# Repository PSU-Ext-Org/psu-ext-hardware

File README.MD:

<h1 align="center">PSU-EXT Hardware</h1>

<p align="center">
  An open-hardware inline extension that adds measurement, protection, and
  programmable control to an existing bench power supply.
</p>

<p align="center">

</p>

> **EVT prototype:** PSU-EXT is an engineering-validation design, not a
> finished or certified consumer product. It extends a bench PSU; it is not a
> standalone power supply. Use it only within the stated ratings and with
> appropriate laboratory safety practices.

## What it does

PSU-EXT sits between a bench power supply and a load or device under test. It
measures output voltage and current, controls the output path with a relay, and
makes the setup easier to monitor and automate.

- Live voltage, current, and power telemetry
- Relay-controlled output enable/disable
- Galvanically isolated control and measurement domains
- SCPI control over USB CDC and TCP through the companion firmware and software
- External trigger inputs, timer support, and configurable OVP/OCP behaviour

## Hardware at a glance

> **Warning:** PSU-EXT does not provide reverse-polarity protection. Verify
> supply and load polarity before connecting the device.

| Item | Details |
| --- | --- |
| Operating range | 0–25 V, 0–2.5 A |
| Board size | 100 × 50 mm (3.94 × 1.97 in) |
| Control connection | USB-C for power and data |
| Controller | Espressif ESP32-S3 |
| Measurement | ADS1115 ADC and INA240 current-sense front end |
| Isolation | Isolated I²C and isolated DC-DC power for the measurement domain |

## Repository contents

- [`electronics/`](electronics/) — KiCad schematics, PCB, libraries, and the
  [schematic PDF export](electronics/exports/schematic.pdf)
- [`mechanical/`](mechanical/) — FreeCAD enclosure design and label artwork
- [`manufacturing/`](manufacturing/) — Gerbers, BOM, and pick-and-place (CPL)
  files for fabrication and assembly
- [`THIRD-PARTY-NOTICES.md`](THIRD-PARTY-NOTICES.md) — attribution and licence
  information for bundled library assets

The design was created with [**FreeCAD 1.1.1**](https://www.freecad.org/) and
[**KiCad 10.0.1**](https://www.kicad.org/).

## Related PSU-EXT projects

- [PSU-EXT Root](https://github.com/PSU-Ext-Org/psu-ext)
- [Firmware](https://github.com/PSU-Ext-Org/psu-ext-firmware)
- [Control software](https://github.com/PSU-Ext-Org/psu-ext-software)

## Licence

Original PSU-EXT hardware design sources are licensed under the
[CERN Open Hardware Licence Version 2 - Strongly Reciprocal](LICENCE)
(CERN-OHL-S v2). The source location is
<https://github.com/PSU-Ext-Org/psu-ext>.

Some library assets are separately licensed. See [NOTICE](NOTICE),
[THIRD-PARTY-NOTICES.md](THIRD-PARTY-NOTICES.md), and
[LICENSES/dep5](LICENSES/dep5) before copying or modifying them.

Changes to the design are recorded in [CHANGES.txt](CHANGES.txt).

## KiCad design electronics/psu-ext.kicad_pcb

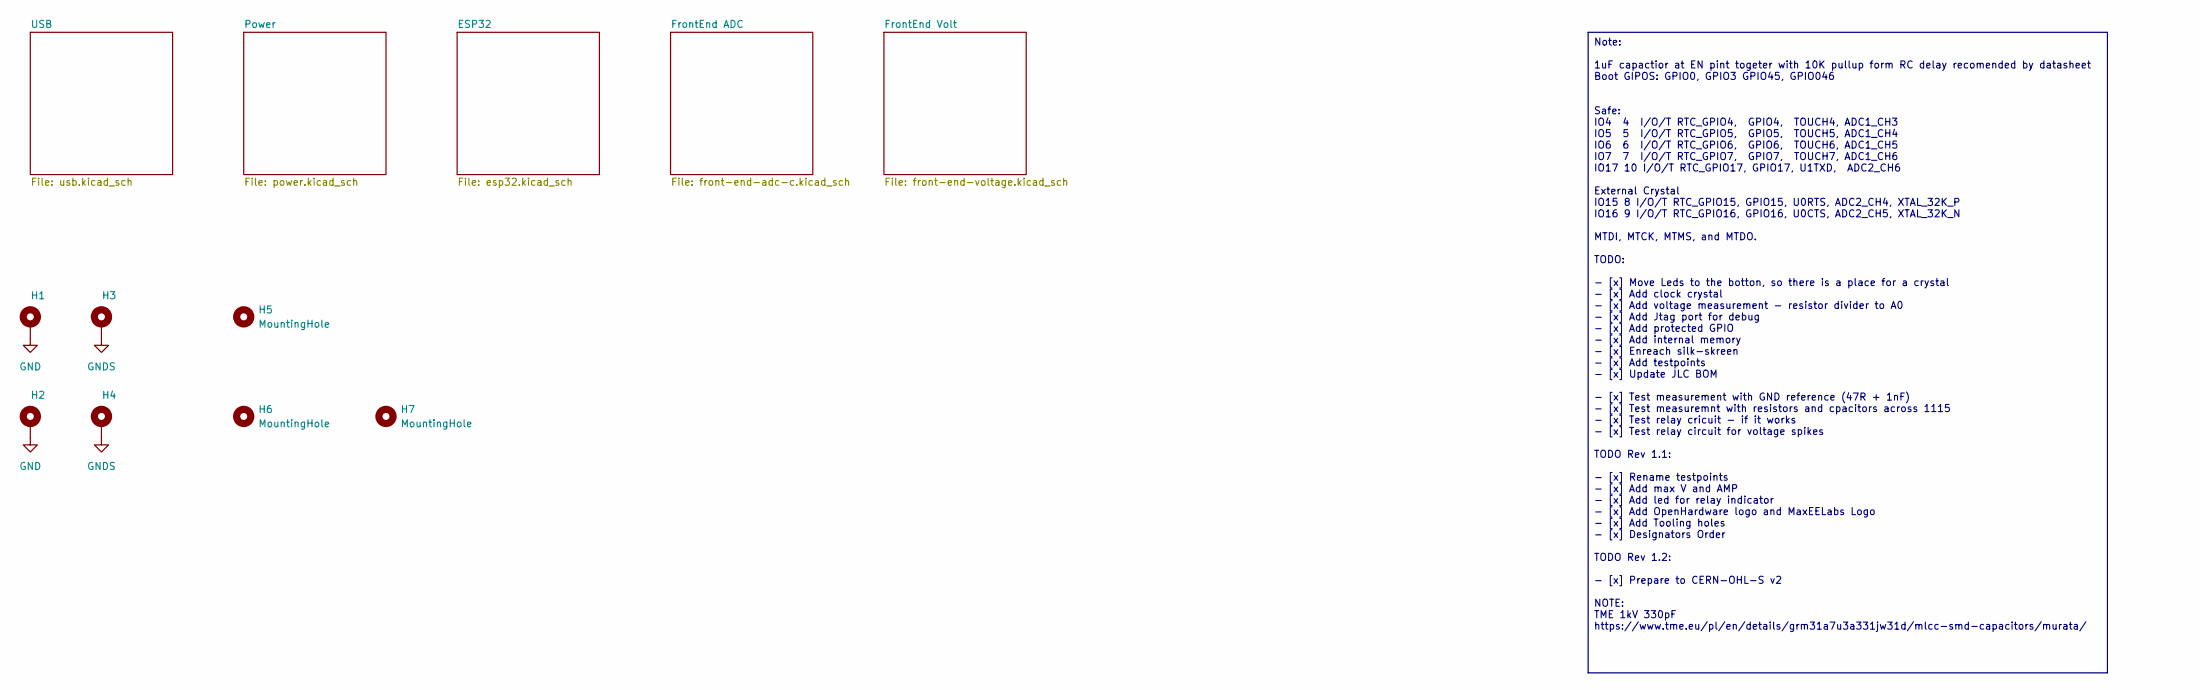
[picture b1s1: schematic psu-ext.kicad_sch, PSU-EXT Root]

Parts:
H1, H2, H3, H4: MountingHole_Pad; MountingHole_3.2mm_M3_ISO7380_Pad
H5, H6, H7: MountingHole; ToolingHole_1.152mm

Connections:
GND: H1.1 (1_1), H2.1 (1_1); also elsewhere on the board
GNDS: H3.1 (1_1), H4.1 (1_1); also elsewhere on the board

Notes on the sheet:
Note: 1uF capactior at EN pint togeter with 10K pullup form RC delay recomended by datasheet Boot GIPOS: GPIO0, GPIO3 GPIO45, GPIO046 Safe: IO4 4 I/O/T RTC_GPIO4, GPIO4, TOUCH4, ADC1_CH3 IO5 5 I/O/T RTC_GPIO5, GPIO5, TOUCH5, ADC1_CH4 IO6 6 I/O/T RTC_GPIO6, GPIO6, TOUCH6, ADC1_CH5 IO7 7 I/O/T RTC_GP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

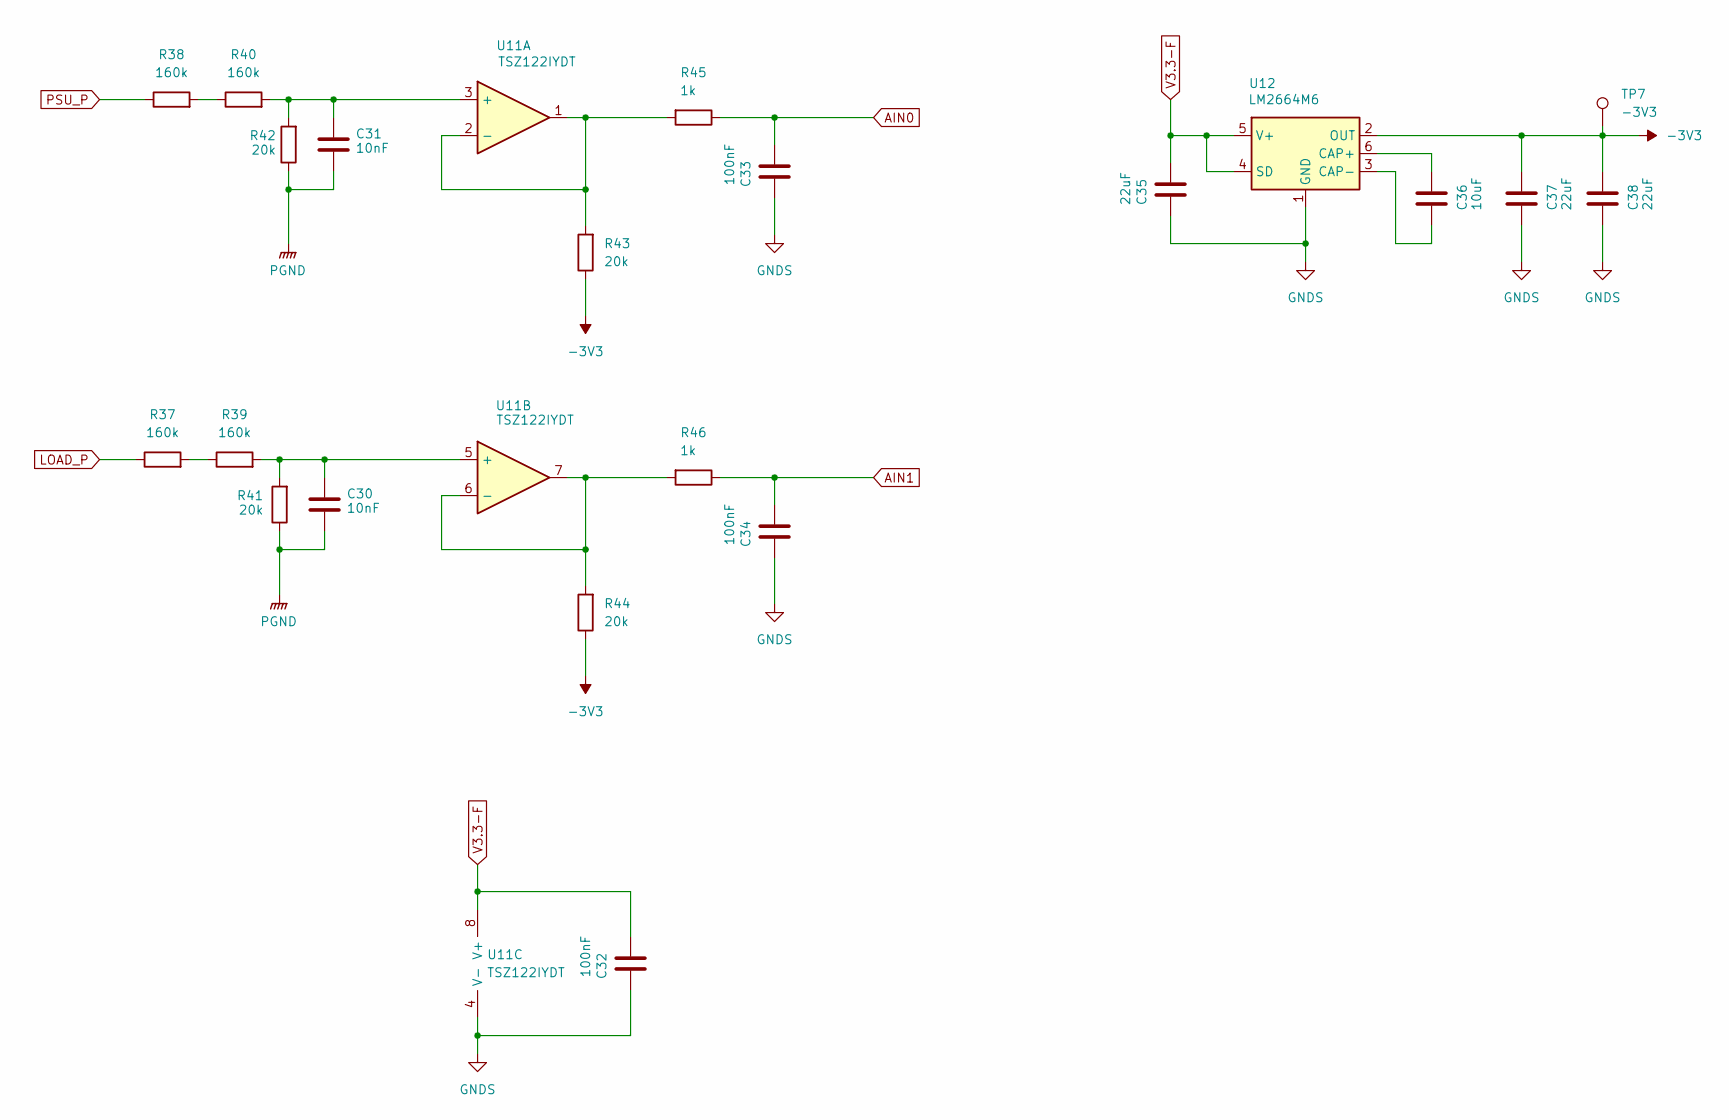
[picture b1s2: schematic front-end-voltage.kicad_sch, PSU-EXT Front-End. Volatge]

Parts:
C30, C31: 10nF; C_0805_2012Metric
C32, C33, C34: 100nF; C_0805_2012Metric
C35, C37, C38: 22uF; C_0805_2012Metric
C36: 10uF; C_0805_2012Metric
R37, R38, R39, R40: 160k; R_0805_2012Metric
R41, R42, R43, R44: 20k; R_0805_2012Metric
R45, R46: 1k; R_0805_2012Metric
TP7: -3V3; TestPoint_Pad_D1.5mm
U11: TSZ122IYDT; SOIC-8_3.9x4.9mm_P1.27mm
U12: LM2664M6; SOT-23-6

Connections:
-3V3: C37.1, C38.1, R43.1, R44.1, TP7.1 (1_1), U12.2 (OUT)
AIN0: C33.1, R45.1; also elsewhere on the board
AIN1: C34.1, R46.1; also elsewhere on the board
GNDS: C32.2, C33.2, C34.2, C35.2, C37.2, C38.2, U11.4 (V-), U12.1 (GND); also elsewhere on the board
LOAD_P: R37.1; also elsewhere on the board
unnamed: R37.2, R39.1
unnamed: R38.2, R40.1
unnamed: C31.1, R40.2, R42.2, U11.3 (+)
unnamed: R43.2, R45.2, U11.1, U11.2 (-)
unnamed: C30.1, R39.2, R41.2, U11.5 (+)
unnamed: R44.2, R46.2, U11.6 (-), U11.7
unnamed: C36.1, U12.6 (CAP+)
unnamed: C36.2, U12.3 (CAP-)
PGND: C30.2, C31.2, R41.1, R42.1; also elsewhere on the board
PSU_P: R38.1; also elsewhere on the board
V3.3-F: C32.1, C35.1, U11.8 (V+), U12.4 (SD), U12.5 (V+); also elsewhere on the board

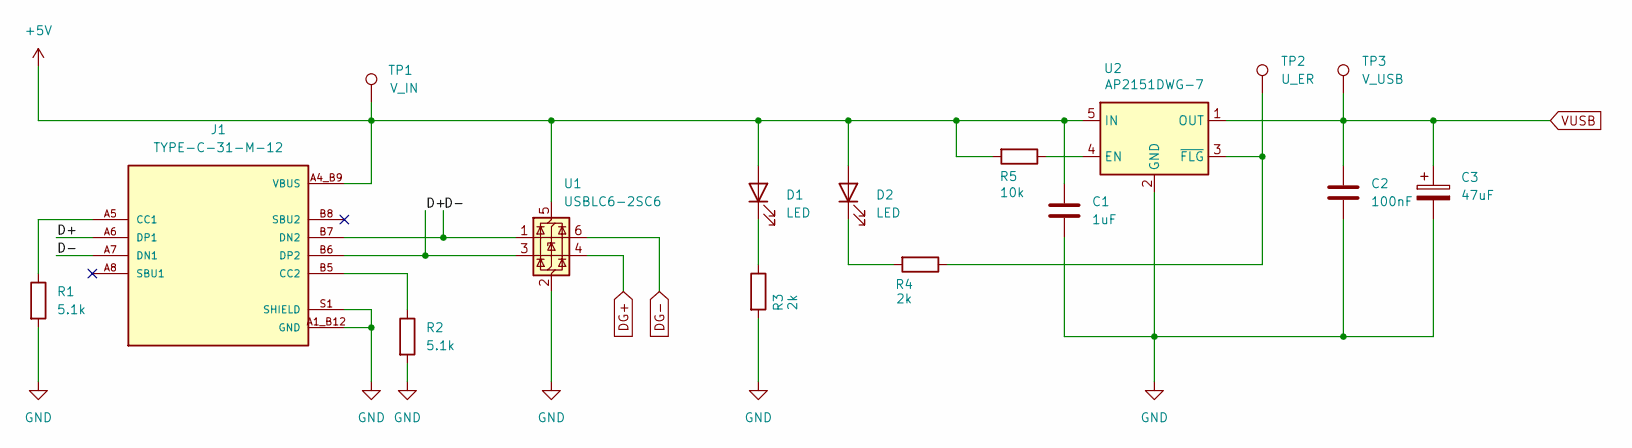
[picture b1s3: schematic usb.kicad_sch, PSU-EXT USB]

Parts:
C1: 1uF; C_0805_2012Metric
C2: 100nF; C_0805_2012Metric
C3: 47uF; CP_Elec_5x5.9
D1, D2: LED; LED_0805_2012Metric
J1: TYPE-C-31-M-12; HRO_TYPE-C-31-M-12; PARTREV 2020.12.08
R1, R2: 5.1k; R_0805_2012Metric
R3, R4: 2k; R_0805_2012Metric
R5: 10k; R_0805_2012Metric
TP1: V_IN; TestPoint_Pad_D1.5mm
TP2: U_ER; TestPoint_Pad_D1.5mm
TP3: V_USB; TestPoint_Pad_D1.5mm
U1: USBLC6-2SC6; SOT-23-6
U2: AP2151DWG-7; SOT-23-5

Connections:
+5V: C1.1, D1.2 (A), D2.2 (A), J1.A4_B9 (VBUS), J1.B4_A9 (VBUS), R5.2, TP1.1 (1_1), U1.5 (VBUS), U2.5 (IN)
/USB/D+: J1.A6 (DP1), J1.B6 (DP2), U1.3 (I/O2)
/USB/D-: J1.A7 (DN1), J1.B7 (DN2), U1.1 (I/O1)
DG+: U1.4 (I/O2); also elsewhere on the board
DG-: U1.6 (I/O1); also elsewhere on the board
GND: C1.2, C2.2, C3.2, J1.A1_B12 (GND), J1.B1_A12 (GND), J1.S1 (SHIELD), J1.S2 (SHIELD), J1.S3 (SHIELD), J1.S4 (SHIELD), R1.2, R2.2, R3.2, U1.2 (GND), U2.2 (GND); also elsewhere on the board
unnamed: D1.1 (K), R3.1
unnamed: D2.1 (K), R4.2
unnamed: J1.A5 (CC1), R1.1
unnamed: J1.B5 (CC2), R2.1
unnamed: R5.1, U2.4 (EN)
unnamed: R4.1, TP2.1 (1_1), U2.3 (~FLG)
VUSB: C2.1, C3.1, TP3.1 (1_1), U2.1 (OUT); also elsewhere on the board

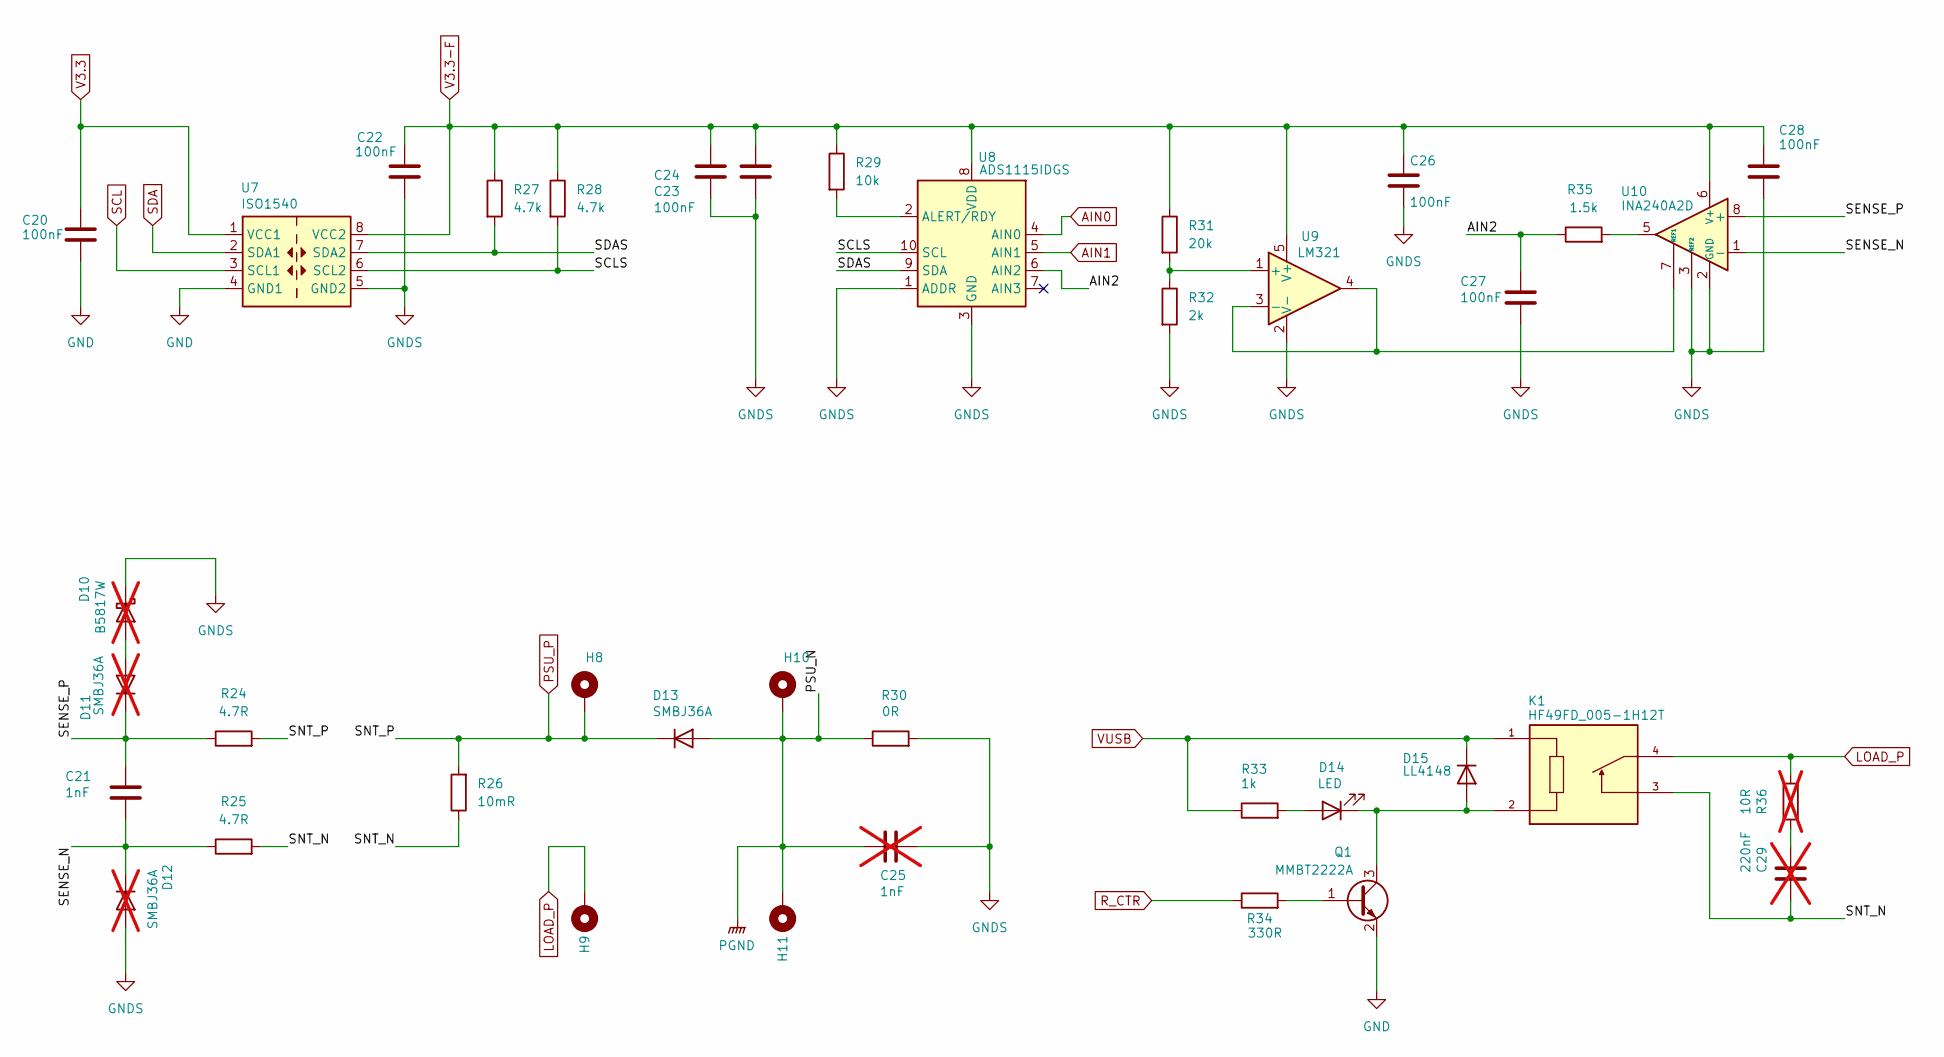
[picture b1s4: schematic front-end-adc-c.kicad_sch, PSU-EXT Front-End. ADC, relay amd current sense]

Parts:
C20, C22, C23, C24, C26, C27, C28: 100nF; C_0805_2012Metric
C21: 1nF; C_0805_2012Metric
C25: 1nF; C_0805_2012Metric; not fitted
C29: 220nF; C_0805_2012Metric; not fitted
D10: B5817W; Nexperia_CFP3_SOD-123W; not fitted
D11, D12: SMBJ36A; D_SMB; not fitted
D13: SMBJ36A; D_SMB
D14: LED; LED_0805_2012Metric
D15: LL4148; D_MiniMELF
H8, H9, H10, H11: MountingHole_Pad; MountingHole_4.3mm_M4_ISO7380_Pad
K1: HF49FD_005-1H12T; RELAY_HF49FD_005-1H12T; PARTREV 1.13
Q1: MMBT2222A; SOT-23
R24, R25: 4.7R; R_0805_2012Metric
R26: 10mR; R_2512_6332Metric_Pad1.40x3.35mm_HandSolder
R27, R28: 4.7k; R_0805_2012Metric
R29: 10k; R_0805_2012Metric
R30: 0R; R_0805_2012Metric
R31: 20k; R_0805_2012Metric
R32: 2k; R_0805_2012Metric
R33: 1k; R_0805_2012Metric
R34: 330R; R_0805_2012Metric
R35: 1.5k; R_0805_2012Metric
R36: 10R; R_0805_2012Metric; not fitted
U7: ISO1540; SOIC-8_3.9x4.9mm_P1.27mm
U8: ADS1115IDGS; TSSOP-10_3x3mm_P0.5mm
U9: LM321; SOT-23-5
U10: INA240A2D; SOIC-8_3.9x4.9mm_P1.27mm

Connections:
/FrontEnd ADC/AIN2: C27.1, R35.1, U8.6 (AIN2)
/FrontEnd ADC/SCLS: R28.2, U7.6 (SCL2), U8.10 (SCL)
/FrontEnd ADC/SDAS: R27.2, U7.7 (SDA2), U8.9 (SDA)
/FrontEnd ADC/SENSE_N: C21.2, D12.1 (K), R25.1, U10.1 (-)
/FrontEnd ADC/SENSE_P: C21.1, D11.1 (K), R24.1, U10.8 (+)
/FrontEnd ADC/SNT_N: C29.2, K1.3, R25.2, R26.1
AIN0: U8.4 (AIN0); also elsewhere on the board
AIN1: U8.5 (AIN1); also elsewhere on the board
GND: C20.2, Q1.2 (E), U7.4 (GND1); also elsewhere on the board
GNDS: C22.2, C23.2, C24.2, C25.2, C26.2, C27.2, C28.2, D10.1 (K), D12.2 (A), R30.2, R32.2, U7.5 (GND2), U8.1 (ADDR), U8.3 (GND), U9.2 (V-), U10.2 (GND), U10.3 (REF2), U10.4 (GND); also elsewhere on the board
LOAD_P: H9.1 (1_1), K1.4, R36.1; also elsewhere on the board
unnamed: C29.1, R36.2
unnamed: D10.2 (A), D11.2 (A)
unnamed: D14.2 (A), R33.2
unnamed: D14.1 (K), D15.2 (A), K1.2, Q1.3 (C)
unnamed: Q1.1 (B), R34.2
unnamed: R35.2, U10.5
unnamed: R29.2, U8.2 (ALERT/RDY)
unnamed: R31.2, R32.1, U9.1 (+)
unnamed: U9.3 (-), U9.4, U10.7 (REF1)
PGND: C25.1, D13.2 (A), H10.1 (1_1), H11.1 (1_1), R30.1; also elsewhere on the board
PSU_P: D13.1 (K), H8.1 (1_1), R24.2, R26.2; also elsewhere on the board
R_CTR: R34.1; also elsewhere on the board
SCL: U7.3 (SCL1); also elsewhere on the board
SDA: U7.2 (SDA1); also elsewhere on the board
V3.3: C20.1, U7.1 (VCC1); also elsewhere on the board
V3.3-F: C22.1, C23.1, C24.1, C26.1, C28.1, R27.1, R28.1, R29.1, R31.1, U7.8 (VCC2), U8.8 (VDD), U9.5 (V+), U10.6 (V+); also elsewhere on the board
VUSB: D15.1 (K), K1.1, R33.1; also elsewhere on the board

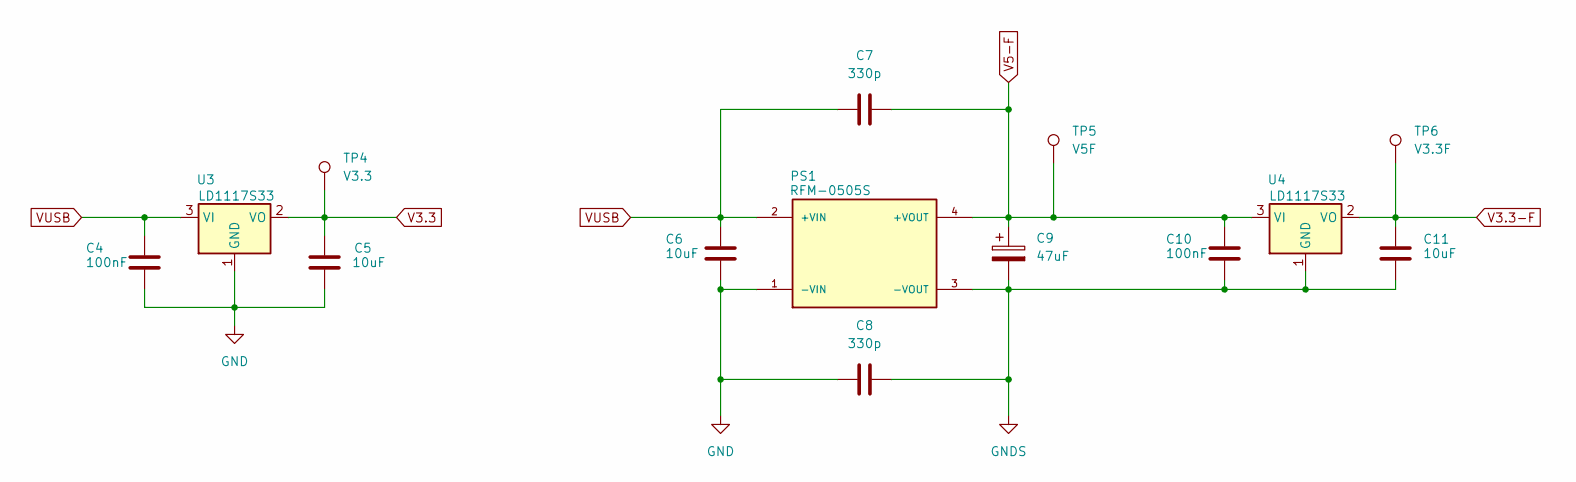
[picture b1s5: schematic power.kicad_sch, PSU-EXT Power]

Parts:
C4, C10: 100nF; C_0805_2012Metric
C5, C11: 10uF; C_1206_3216Metric
C6: 10uF; C_0805_2012Metric
C7, C8: 330p; C_1206_3216Metric_Pad1.33x1.80mm_HandSolder
C9: 47uF; CP_Elec_5x5.9
PS1: RFM-0505S; CONV_RFM-0505S; PARTREV 0
TP4: V3.3; TestPoint_Pad_D1.5mm
TP5: V5F; TestPoint_Pad_D1.5mm
TP6: V3.3F; TestPoint_Pad_D1.5mm
U3, U4: LD1117S33; SOT-223-3_TabPin2

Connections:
GND: C4.2, C5.2, C6.2, C8.1, PS1.1 (-VIN), U3.1 (GND); also elsewhere on the board
GNDS: C8.2, C9.2, C10.2, C11.2, PS1.3 (-VOUT), U4.1 (GND); also elsewhere on the board
V3.3: C5.1, TP4.1 (1_1), U3.2 (VO); also elsewhere on the board
V3.3-F: C11.1, TP6.1 (1_1), U4.2 (VO); also elsewhere on the board
V5-F: C7.2, C9.1, C10.1, PS1.4 (+VOUT), TP5.1 (1_1), U4.3 (VI)
VUSB: C4.1, C6.1, C7.1, PS1.2 (+VIN), U3.3 (VI); also elsewhere on the board

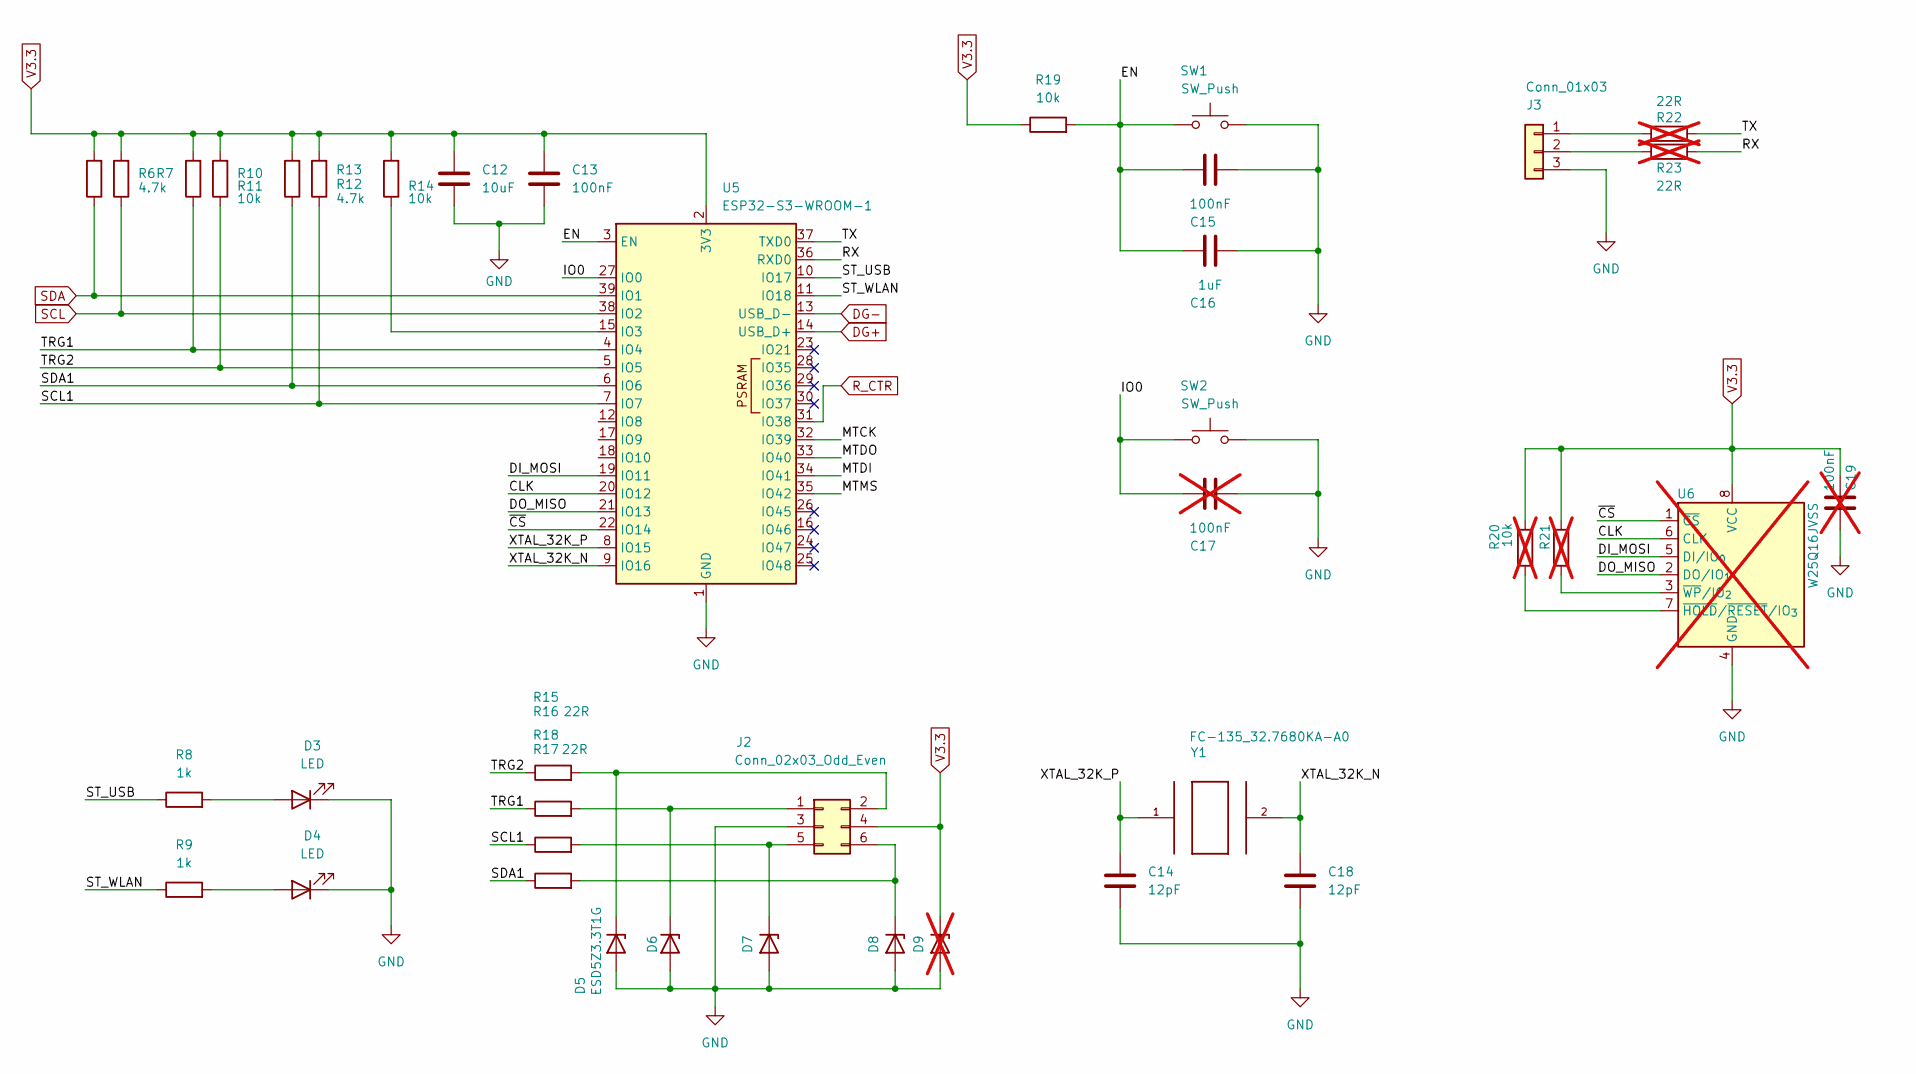
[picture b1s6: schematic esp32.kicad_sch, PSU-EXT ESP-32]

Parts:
C12: 10uF; C_0805_2012Metric
C13, C15: 100nF; C_0805_2012Metric
C14, C18: 12pF; C_0805_2012Metric
C16: 1uF; C_0805_2012Metric
C17, C19: 100nF; C_0805_2012Metric; not fitted
D3, D4: LED; LED_0805_2012Metric
D5, D6, D7, D8: ESD5Z3.3T1G; D_SOD-523
D9: ESD5Z3.3T1G; D_SOD-523; not fitted
J2: Conn_02x03_Odd_Even; PinHeader_2x03_P2.54mm_Vertical
J3: Conn_01x03; PinHeader_1x03_P2.54mm_Vertical
R6, R7, R12, R13: 4.7k; R_0805_2012Metric
R8, R9: 1k; R_0805_2012Metric
R10, R11, R14, R19: 10k; R_0805_2012Metric
R15, R16, R17, R18: 22R; R_0805_2012Metric
R20, R21: 10k; R_0805_2012Metric; not fitted
R22, R23: 22R; R_0805_2012Metric; not fitted
SW1, SW2: SW_Push; SW_SPST_TS-1088-xR025
U5: ESP32-S3-WROOM-1
U6: W25Q16JVSS; SOIC-8_5.3x5.3mm_P1.27mm; not fitted
Y1: FC-135_32.7680KA-A0; XTAL_FC-135_32.7680KA-A0

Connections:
/ESP32/CLK: U5.20 (IO12), U6.6 (CLK)
/ESP32/DI_MOSI: U5.19 (IO11), U6.5 (DI/IO_{0})
/ESP32/DO_MISO: U5.21 (IO13), U6.2 (DO/IO_{1})
/ESP32/EN: C15.1, C16.1, R19.2, SW1.1, U5.3 (EN)
/ESP32/IO0: C17.1, SW2.1, U5.27 (IO0)
/ESP32/MTCK: U5.32 (IO39)
/ESP32/MTDI: U5.34 (IO41)
/ESP32/MTDO: U5.33 (IO40)
/ESP32/MTMS: U5.35 (IO42)
/ESP32/RX: R23.2, U5.36 (RXD0)
/ESP32/SCL1: R13.1, R17.1, U5.7 (IO7)
/ESP32/SDA1: R12.1, R18.1, U5.6 (IO6)
/ESP32/ST_USB: R8.1, U5.10 (IO17)
/ESP32/ST_WLAN: R9.1, U5.11 (IO18)
/ESP32/TRG1: R10.1, R16.1, U5.4 (IO4)
/ESP32/TRG2: R11.1, R15.1, U5.5 (IO5)
/ESP32/TX: R22.2, U5.37 (TXD0)
/ESP32/XTAL_32K_N: C18.1, U5.9 (IO16), Y1.2
/ESP32/XTAL_32K_P: C14.1, U5.8 (IO15), Y1.1
/ESP32/~CS: U5.22 (IO14), U6.1 (~CS)
DG+: U5.14 (USB_D+); also elsewhere on the board
DG-: U5.13 (USB_D-); also elsewhere on the board
GND: C12.2, C13.2, C14.2, C15.2, C16.2, C17.2, C18.2, C19.1, D3.1 (K), D4.1 (K), D5.2 (A), D6.2 (A), D7.2 (A), D8.2 (A), D9.2 (A), J2.3, J3.3, SW1.2, SW2.2, U5.1 (GND), U5.40 (GND), U5.41 (GND), U6.4 (GND); also elsewhere on the board
unnamed: D3.2 (A), R8.2
unnamed: D4.2 (A), R9.2
unnamed: D5.1 (K), J2.2, R15.2
unnamed: D6.1 (K), J2.1, R16.2
unnamed: D7.1 (K), J2.5, R17.2
unnamed: D8.1 (K), J2.6, R18.2
unnamed: J3.1, R22.1
unnamed: J3.2, R23.1
unnamed: R14.1, U5.15 (IO3)
unnamed: R20.2, U6.7 (~HOLD/~RESET/IO_{3})
unnamed: R21.2, U6.3 (~WP/IO_{2})
R_CTR: U5.31 (IO38); also elsewhere on the board
SCL: R7.1, U5.38 (IO2); also elsewhere on the board
SDA: R6.1, U5.39 (IO1); also elsewhere on the board
V3.3: C12.1, C13.1, C19.2, D9.1 (K), J2.4, R6.2, R7.2, R10.2, R11.2, R12.2, R13.2, R14.2, R19.1, R20.1, R21.1, U5.2 (3V3), U6.8 (VCC); also elsewhere on the board

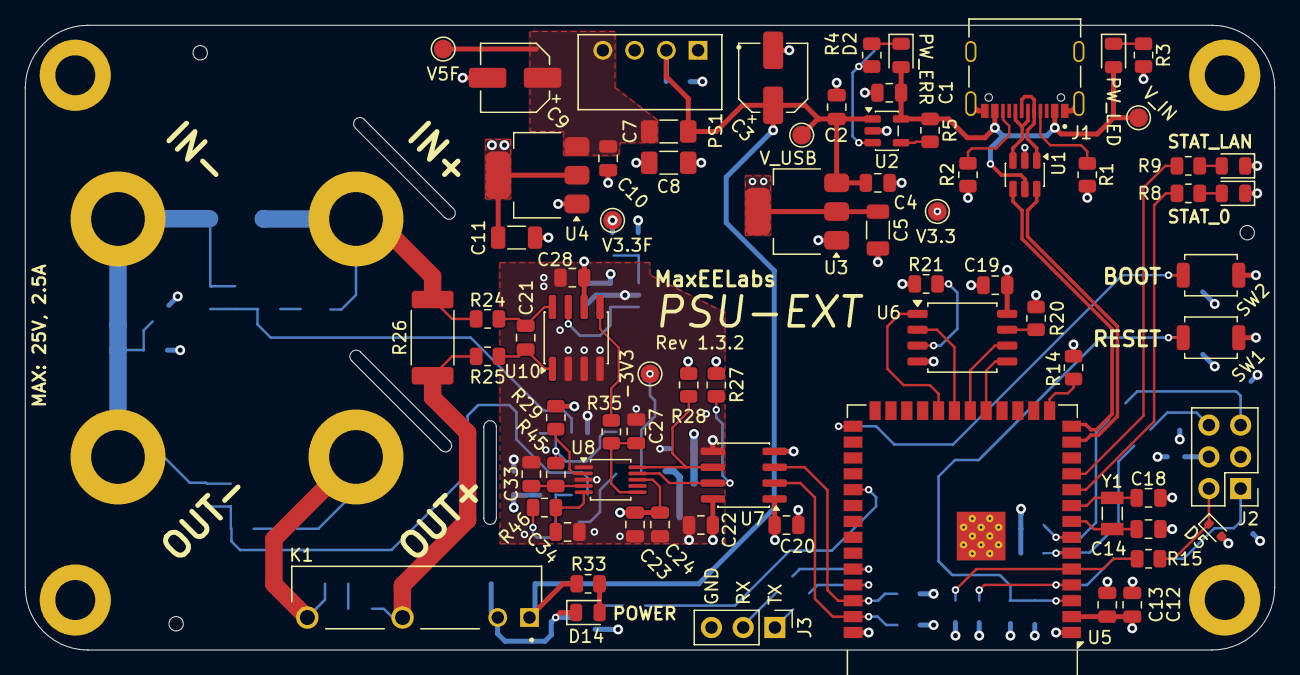
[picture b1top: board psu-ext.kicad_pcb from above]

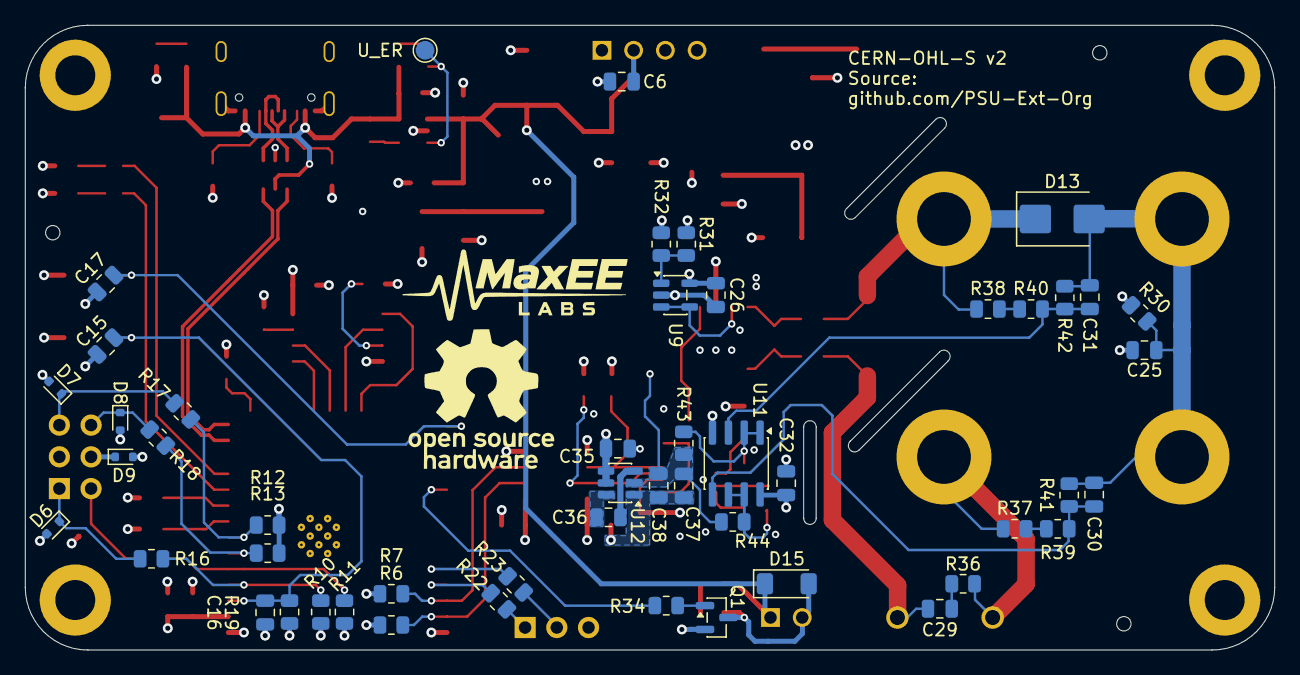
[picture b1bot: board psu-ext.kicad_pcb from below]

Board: 4 copper layers, 100.0 x 50.0 mm, 137 parts (52 on the bottom side), 75 nets.

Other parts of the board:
G1: LOGO; logo_oshw_22x13.2mm
G2: LOGO; logo_20x11.2mm

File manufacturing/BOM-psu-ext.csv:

*Reference,*Manufacturer Part number,*QTY,*Original,Description,Purchase Link
R30,0805W8F0000T5E,1,Y,0Ω ±1% 125mW 0805 Thick Film Resistor,
R35,0805W8F1501T5E,1,Y,1.5kΩ ±1% 125mW 0805 Thick Film Resistor,
"C10,C13,C15,C2,C20,C22,C23,C24,C26,C27,C28,C32,C33,C34,C4",CC0805KRX7R9BB104,15,Y,100nF ±10% 50V Ceramic Capacitor X7R 0805,
"R10,R11,R14,R19,R29,R5",0805W8F1002T5E,6,Y,10kΩ ±1% 125mW 0805 Thick Film Resistor,
R26,25121WF100MT4E,1,Y,10mΩ 1W 200V Thick Film Resistor ±1500ppm/℃ ±1% 2512 Chip Resistor - Surface Mount RoHS,
"C30,C31",CL21B103KBANNNC,2,Y,10nF ±10% 50V Ceramic Capacitor X7R 0805,
"C11,C5",CL31A106KBHNNNE,2,Y,10uF ±10% 50V Ceramic Capacitor X5R 1206,
"C12,C36,C6",CL21A106KAYNNNE,3,Y,10uF ±10% 25V Ceramic Capacitor X5R 0805,
"C14,C18",CC0805JRNPO9BN120,2,Y,12pF ±5% 50V Ceramic Capacitor NP0 0805,
"R37,R38,R39,R40",FRC0805J164 TS,4,Y,160kΩ ±5% 125mW 0805 Thick Film Resistor,
"R33,R45,R46,R8,R9",0805W8F1001T5E,5,Y,1kΩ ±1% 125mW 0805 Thick Film Resistor,
C21,CL21B102KBCNNNC,1,Y,1nF ±10% 50V Ceramic Capacitor X7R 0805,
"C1,C16",CL21B105KBFNNNE,2,Y,1uF ±10% 50V Ceramic Capacitor X7R 0805,
"R31,R41,R42,R43,R44",0805W8F2002T5E,5,Y,20kΩ ±1% 125mW 0805 Thick Film Resistor,
"R15,R16,R17,R18",0805W8F220JT5E,4,Y,22Ω ±1% 125mW 0805 Thick Film Resistor,
"C35,C37,C38",CL21A226MAQNNNE,3,Y,22uF ±20% 25V Ceramic Capacitor X5R 0805,
"R3,R32,R4",0805W8J0202T5E,3,Y,2kΩ ±5% 125mW 0805 Thick Film Resistor,
R34,0805W8F3300T5E,1,Y,330Ω ±1% 125mW 0805 Thick Film Resistor,
"C7,C8",TCC1206COG331J102DT,2,Y,330pF ±5% 1kV Ceramic Capacitor C0G 1206,
"R24,R25",0805W8F470KT5E,2,Y,4.7Ω ±1% 125mW 0805 Thick Film Resistor,
"R12,R13,R27,R28,R6,R7",0805W8F4701T5E,6,Y,4.7kΩ ±1% 125mW 0805 Thick Film Resistor,
"C3,C9",189RV0006,2,Y,47uF ±20% 35V Aluminum Electrolytic Capacitors 2000hrs@105℃,
"R1,R2",0805W8F5101T5E,2,Y,5.1kΩ ±1% 125mW 0805 Thick Film Resistor,
U8,ADS1115IDGSR,1,Y,I2C 2V~5.5V VSSOP-10 Analog to Digital Converters (ADC) RoHS,
U2,AP2151DWG-7,1,Y,"Current limited 0.8A power switch, single channel, SOT-23-5",
J3,2.54-1*3P,1,Y,Pin Header 3 Position 2.54mm Pitch Single Row Through Hole -40℃~+105℃,
J2,2.54-2*3P,1,Y,Pin Header 6 Position 2.54mm Pitch Dual Row Through Hole,
"D5,D6,D7,D8",ESD5Z3.3T1G,4,Y,14VC Clamp 11A Ipp ESD DIODE SOD-523,
U5,ESP32-S3-WROOM-1-N16R8,1,Y,"2.4GHz ESP32-S3R8 On-board PCB Antenna -103.5dBm SMD,25.5x18mm RF Transceiver Modules and Modems RoHS",
Y1,FC-135R 32.7680KA-A3,1,Y,Crystal 32.768kHz ±20ppm 12.5pF 50kΩ SMD3215-2P,
K1,HF49FD/005-1H12T,1,Y,"Power Relay 1 Form A: 1A (SPST-NO) 5V Coil SIP,5x20mm",
U10,INA240A2DR,1,Y,"1 5uV -4V~80V 2V/us 132dB 90uA 1.8mA 50V/V SOIC-8 Instrumentation, Op Amps, Buffer Amps RoHS",
U7,ISO1540DR,1,Y,50kV/us 3V~5.5V SOIC-8 Digital Isolators RoHS,
"U3,U4",LD1117S33TR,2,Y,"3.3V Positive Fixed SOT-223 Voltage Regulators - Linear, Low Drop Out (LDO) Regulators RoHS",
D3,KT-0805G,1,Y,Emerald Green 525nm LED Indication - Discrete 2.6V~3.1V 0805,
D4,KT-0805W,1,Y,White LED Indication - Discrete 2.6V~3.2V 0805,
"D1,D14,D2",NCD0805R1,3,Y,Red 630nm LED Indication - Discrete 1.6V~2.6V 0805,
D15,LL4148-GS08,1,Y,Diode Independent 75V 300mA Surface Mount MiniMELF,
U12,LM2664M6X/NOPB,1,Y,Inverted 80kHz -5.5V~-1.8V 40mA SOT-23-6 Voltage Regulators - DC DC Switching Regulators RoHS,
U9,LMV321LILT,1,Y,"70mA 1 7mV 600V/ms 75dB 27nA 120uA 1.3MHz Rail-to-rail output SOT-23-5 Instrumentation, Op Amps, Buffer Amps RoHS",
Q1,MMBT2222A 1P,1,Y,Bipolar (BJT) Transistor NPN 40V 600mA 300MHz 300mW Surface Mount SOT-23,
PS1,RFM-0505S,1,Y,Isolated Module DC DC Converter 1 Output 5V 200mA 5V Input,
D13,SMBJ36A,1,Y,58.1VC Clamp 10.4A@10/1000us Ipp TVS DIODE DO-214AA(SMB),
"SW1,SW2",TS-1088-AR02016,2,Y,Tactile Switch SPST 160gf 2mm SMD (SMT) Tab 4mm x 3mm Surface Mount,
U11,TSZ122IYDT,1,Y,"7mA 2 1uV 0.19V/us 122dB 70pA 28uA 400kHz Rail-to-Rail Input, Rail-to-Rail Output SO-8 Instrumentation, Op Amps, Buffer Amps RoHS",
J1,TYPE-C-31-M-12,1,Y,USB-C (USB TYPE-C) Receptacle Connector 16 Position Surface Mount,
U1,USBLC6-2SC6,1,Y,15VC Clamp ESD DIODE SOT-23-6,

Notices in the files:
README.MD:
License: CERN-OHL-S v2
electronics/esp32.kicad_sch:
This hardware design is licensed under CERN-OHL-S v2.
Copyright © 2026 PSU-EXT Authors: https://github.com/PSU-Ext-Org
electronics/psu-ext.kicad_sch:
TODO Rev 1.2:
- [x] Prepare to CERN-OHL-S v2
